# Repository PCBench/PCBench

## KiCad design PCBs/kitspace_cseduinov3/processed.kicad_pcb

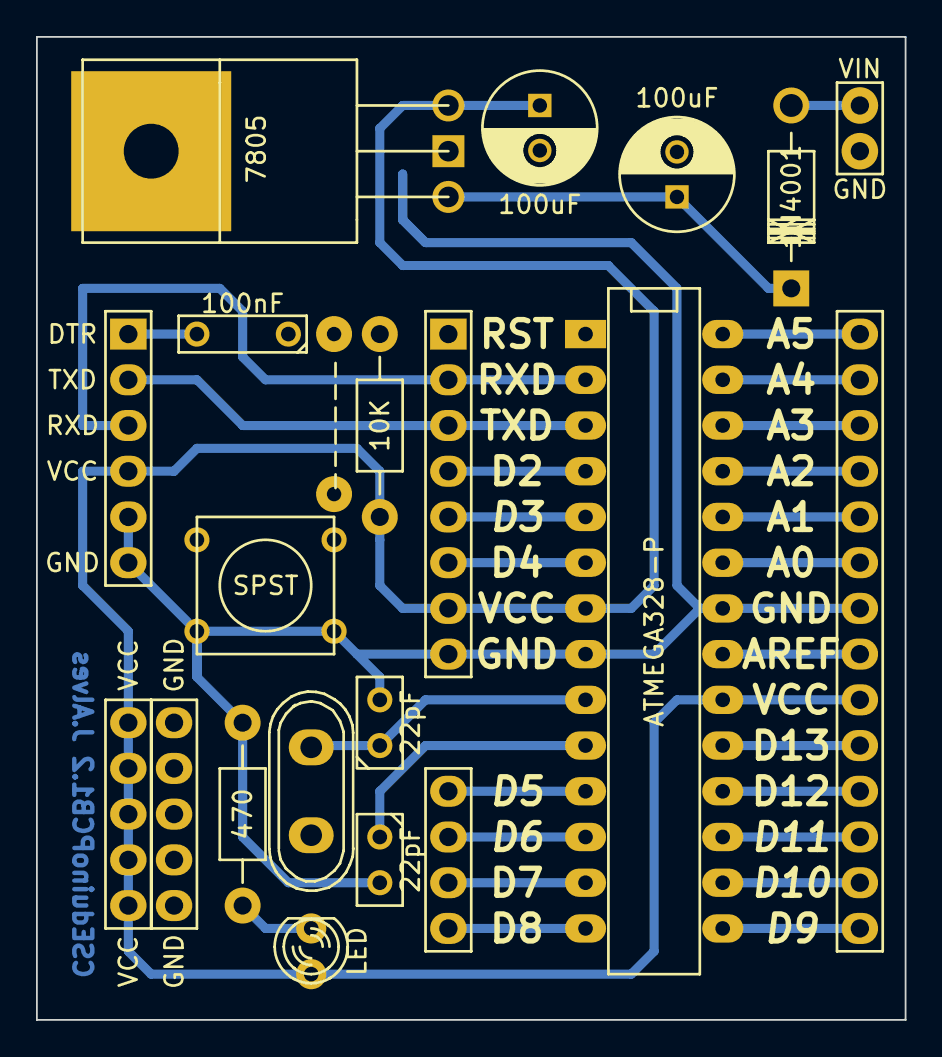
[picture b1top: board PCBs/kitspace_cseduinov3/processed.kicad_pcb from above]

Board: 2 copper layers, 48.3 x 54.6 mm, 18 parts (0 on the bottom side), 29 nets.

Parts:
C1, C2: 100uF; C_Radial_D6.3_L11.2_P2.5
C3, C4: 22pF; C1
C5: 100nF; C2
D1: 1N4001; Diode_DO-41_SOD81_Horizontal_RM10
D2: LED; LED-3MM
IC1: ATMEGA328-P; DIP-28__300_ELL
P1: CONN_01X02; Pin_Header_Straight_1x02
P2: CONN_01X14; Pin_Header_Straight_1x14
P3: CONN_01X04; Pin_Header_Straight_1x04
P4: CONN_01X08; Pin_Header_Straight_1x08
P5: CONN_01X06; Pin_Header_Straight_1x06
R1: 470; Resistor_Horizontal_RM10mm
R2: 10K; Resistor_Horizontal_RM10mm
SW1: SPST; SW_PUSH_SMALL
U1: 7805; LM78XX
X1: CRYSTAL; Crystal_HC50-U_Vertical

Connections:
+5V: C2.1, D2.1, P2.6, P4.7, R2.1
GND: C3.2, C4.2, IC1.8, P2.8, P4.8, P5.5, P5.6, R1.2, SW1.2
unnamed: C1.1, D1.2, U1.VI
unnamed: C3.1, IC1.10
unnamed: C4.1, IC1.9, X1.2
unnamed: C5.2, P5.1
unnamed: D1.1, P1.1
unnamed: D2.2, R1.1
unnamed: IC1.2, P4.2, P5.3
unnamed: IC1.3, P4.3, P5.2
unnamed: IC1.4, P4.4
unnamed: IC1.5, P4.5
unnamed: IC1.6, P4.6
unnamed: IC1.11, P3.1
unnamed: IC1.12, P3.2
unnamed: IC1.13, P3.3
unnamed: IC1.14, P3.4
unnamed: IC1.15, P2.1
unnamed: IC1.16, P2.2
unnamed: IC1.17, P2.3
unnamed: IC1.18, P2.4
unnamed: IC1.19, P2.5
unnamed: IC1.21, P2.7
unnamed: IC1.23, P2.9
unnamed: IC1.24, P2.10
unnamed: IC1.25, P2.11
unnamed: IC1.26, P2.12
unnamed: IC1.27, P2.13
unnamed: IC1.28, P2.14

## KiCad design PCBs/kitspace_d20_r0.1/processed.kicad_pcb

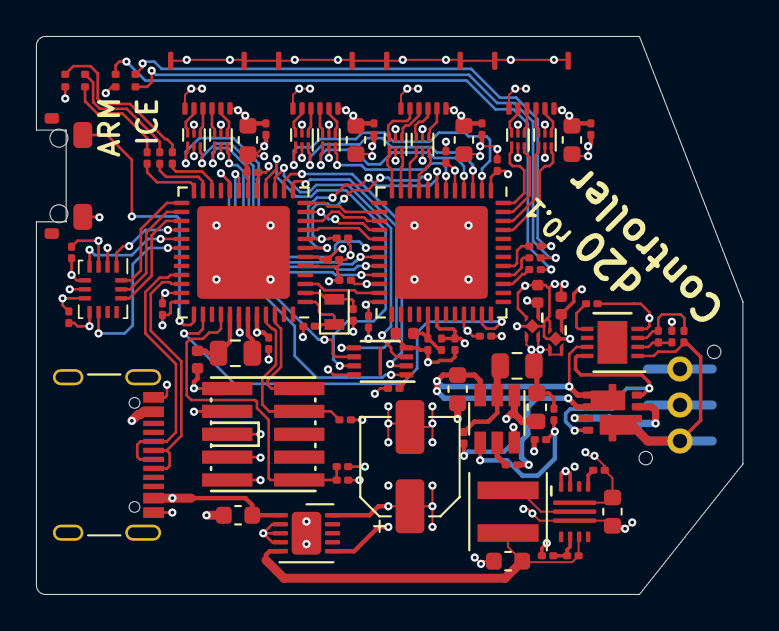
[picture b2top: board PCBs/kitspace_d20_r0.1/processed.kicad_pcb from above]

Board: 4 copper layers, 39.2 x 31.0 mm, 89 parts (1 on the bottom side), 96 nets.

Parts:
C1, C2, C4, C5, C24, C26, C28, C30, C35: 10uF; C_0603_1608Metric
C3, C10, C11, C12, C13, C17, C18, C19, C20, C21, C22, C23, C25, C27, C29, C31, C32, C33, C34: 100nF; C_0201_0603Metric
C6, C7, C8, C14: 1uF; C_0402_1005Metric
C9: CP1; CP_Elec_5x3.9
C15, C16: 22pF; C_0201_0603Metric
D1, D2: LED_ARGB; led_rbag_1515
FB1: Ferrite_Bead_Small; L_0201_0603Metric
J1: Conn_01x03; 3P_Battery_Connector
J2, J3, J4, J5: Conn_01x06_Shielded; 5034800600
J6: Conn_02x05_Odd_Even; FTSH-105-XX-X-DV
J7: USB_C_Receptacle_USB2.0; USB_C_Receptacle_Palconn_UTC16-G
L1: 1uH; L_Coilcraft_XxL4020
L2: 2.2uH; L_0805_2012Metric
L3: 10uH; L_0805_2012Metric
R1, R6: 510k; R_0201_0603Metric
R2: 25.3k; R_0201_0603Metric
R3: 34.8k; R_0201_0603Metric
R4: 750k; R_0201_0603Metric
R5, R8: 100k; R_0201_0603Metric
R7: 93.1k; R_0201_0603Metric
R9: 33.2k; R_0201_0603Metric
R10, R17, R19, R20: 10k; R_0201_0603Metric
R11, R12, R13, R14, R15, R16: 470R; R_0201_0603Metric
R18: 1k; R_0201_0603Metric
SW1: SW_Push; EVQP4
U1: LTC4367; DFN-8-1EP_3x3mm_P0.5mm_EP1.66x2.38mm
U2: AON7804; DFN3X3_8L_EP2_P
U3: TPS62135; VQFN-11_3x2mm_P0.5mm
U4: TPS561201; TSOT-23-6
U5: NP115-2.5; X2SON_4_1.0x1.0mm
U6: NP115-1.2; X2SON_4_1.0x1.0mm
U7: ATSAMD51G19A; QFN-48-1EP_7x7mm_P0.5mm_EP5.15x5.15mm
U8: ICE40UP5K-SG48ITR; QFN-48-1EP_7x7mm_P0.5mm_EP5.15x5.15mm
U9, U10, U11, U12, U13, U14, U15, U16: NC7WZ17; UDFN-6_1x1mm_P0.35mm
U17: BMX160; Bosch_LGA-14_3x2.5mm_P0.5mm
U18: AT25SF081; DFN-8-1EP_3x2mm_Pitch0.5mm
U19: LTC4413-2; DFN-10-1EP_3x3mm_P0.5mm_EP1.65x2.38mm
Y1: 32.768kHz; Crystal_SMD_2012-2Pin_2.0x1.2mm

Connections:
1v2: C7.1, C22.1, C23.1, FB1.1, U6.1, U8.5, U8.30
1v2_pll: C8.1, C21.1, FB1.2, U8.29
2v5: C6.1, C20.1, U5.1, U8.24
3v3: C5.1, C10.1, C11.1, C12.1, C13.1, C17.1, C18.1, C19.1, C33.1, C34.1, D1.1, D2.1, L2.2, R9.2, R18.2, R19.2, R20.2, U5.3, U5.4, U6.3, U6.4, U7.6, U7.17, U7.36, U7.44, U8.1, U8.22, U8.33, U17.5, U17.8, U18.8
3v3_fb: R9.1, R10.1, U4.4
4v5: C9.1, C24.1, C25.1, C26.1, C27.1, C28.1, C29.1, C30.1, C31.1, J2.1, J3.1, J4.1, J5.1, U9.5, U10.5, U11.5, U12.5, U13.5, U14.5, U15.5, U16.5, U19.6, U19.10
4v5_in: C2.1, L1.2, R6.2, U3.6, U19.5
5v0_usb: C35.1, J7.A4, J7.A9, J7.B4, J7.B9, U19.1
5v_fb: R6.1, R7.1, U3.5
unnamed: U2.2, U2.5
unnamed: U1.8, U2.3, U2.6
unnamed: R1.1, U1.5
unnamed: R3.1, R4.2, U1.3
unnamed: R2.1, R3.2, U1.2
unnamed: R5.1, U3.8
unnamed: L1.1, U3.2
unnamed: R8.1, U4.5
unnamed: C3.1, U4.6
unnamed: C3.2, L2.1, U4.2
unnamed: C14.1, L3.2, U7.41
unnamed: R11.1, U7.22
unnamed: R12.1, U7.24
unnamed: R13.1, U7.23
unnamed: C15.1, U7.1, Y1.1
unnamed: C16.1, U7.2, Y1.2
unnamed: R14.1, U8.39
unnamed: R15.1, U8.40
unnamed: R16.1, U8.41
unnamed: U7.38, U8.35
unnamed: U7.3, U8.23
unnamed: SW1.1, U7.37
unnamed: L3.1, U7.43
_led0_blank: U8.20, U9.1
_led0_data: U8.21, U9.3
_led0_latch: U8.19, U10.3
_led0_sclk: U8.18, U10.1
_led1_blank: U8.4, U11.1
_led1_data: U8.6, U11.3
_led1_latch: U8.3, U12.3
_led1_sclk: U8.2, U12.1
_led2_blank: U8.10, U13.1
_led2_data: U8.9, U13.3
_led2_latch: U8.11, U14.3
_led2_sclk: U8.12, U14.1
_led3_blank: U8.46, U15.1
_led3_data: U8.45, U15.3
_led3_latch: U8.47, U16.3
_led3_sclk: U8.48, U16.1
gnd: C1.2, C2.2, C4.2, C5.2, C6.2, C7.2, C8.2, C9.2, C10.2, C11.2, C12.2, C13.2, C14.2, C15.2, C16.2, C17.2, C18.2, C19.2, C20.2, C21.2, C22.2, C23.2, C24.2, C25.2, C26.2, C27.2, C28.2, C29.2, C30.2, C31.2, C32.2, C33.2, C34.2, C35.2, J1.3, J2.6, J2.SH, J3.6, J3.SH, J4.6, J4.SH, J5.6, J5.SH, J6.1, J6.3, J6.5, J6.7, J6.9, J7.A1, J7.A12, J7.B1, J7.B12, J7.S1, R1.2, R2.2, R7.2, R10.2, R17.2, SW1.2, U1.4, U3.3, U3.10, U3.11, U4.1, U5.2, U6.2, U7.5, U7.18, U7.35, U7.42, U7.49, U8.49, U9.2, U10.2, U11.2, U12.2, U13.2, U14.2, U15.2, U16.2, U17.2, U17.3, U17.6, U17.7, U18.4, U19.2, U19.3, U19.4, U19.11
ice_config_done: U7.7, U8.7
ice_config_miso: U7.12, U8.14
ice_config_mosi: U7.9, U8.17
ice_config_reset: R17.1, U7.8, U8.8
ice_config_sck: U7.10, U8.15
ice_config_ss: U7.11, U8.16
ice_led_b: D2.4, R16.2
ice_led_g: D2.3, R15.2
ice_led_r: D2.2, R14.2
imu_cs: U7.27, U17.12
imu_int1: U7.29, U17.4
imu_int2: U7.30, U17.9
imu_miso: U7.28, U17.1
imu_mosi: U7.25, U17.14
imu_sck: U7.26, U17.13
led0_blank: J2.3, U9.6
led0_data: J2.2, U9.4
led0_latch: J2.4, U10.4
led0_sclk: J2.5, U10.6
led1_blank: J3.3, U11.6
led1_data: J3.2, U11.4
led1_latch: J3.4, U12.4
led1_sclk: J3.5, U12.6
led2_blank: J4.3, U13.6
led2_data: J4.2, U13.4
led2_latch: J4.4, U14.4
led2_sclk: J4.5, U14.6
led3_blank: J5.3, U15.6
led3_data: J5.2, U15.4
led3_latch: J5.4, U16.4
led3_sclk: J5.5, U16.6
led_b: D1.4, R13.2
led_g: D1.3, R12.2
led_r: D1.2, R11.2
pp_batt: J1.1, R4.1, U1.1, U2.4
pp_batt_prot: C1.1, C4.1, R5.2, R8.2, U1.7, U2.1, U3.1, U4.3
qspi_bus_cs: R20.1, U7.20, U18.1
qspi_bus_io0: U7.13, U18.5
qspi_bus_io1: U7.14, U18.2
qspi_bus_io2: U7.15, U18.3
qspi_bus_io3: U7.16, U18.7
qspi_bus_sck: U7.19, U18.6
samd_rst: C32.1, J6.10, R19.1, U7.40
samd_usb_n: J7.A7, J7.B7, U7.33
samd_usb_p: J7.A6, J7.B6, U7.34
swdclk: J6.4, R18.1, U7.45
swdio: J6.2, U7.46

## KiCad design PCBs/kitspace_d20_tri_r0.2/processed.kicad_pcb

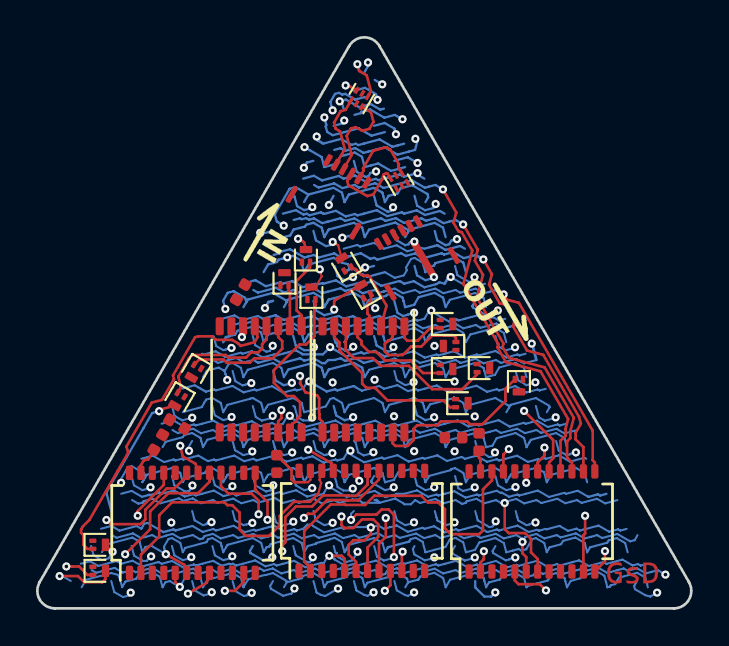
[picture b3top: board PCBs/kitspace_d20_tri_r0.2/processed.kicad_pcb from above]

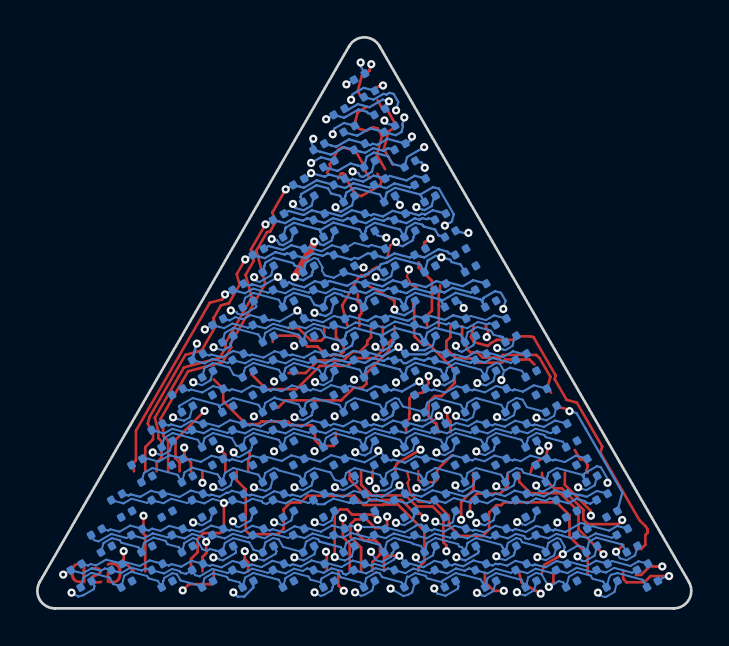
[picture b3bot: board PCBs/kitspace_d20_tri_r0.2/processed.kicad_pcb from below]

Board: 4 copper layers, 36.3 x 31.7 mm, 150 parts (120 on the bottom side), 84 nets.

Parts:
C1, C2, C3: 100nF; C_0402_1005Metric
D1, D2, D3, D4, D5, D6, D7, D8, D9, D10, D11, D12, D13, D14, D15, D17, D18, D19, D20, D21, D22, D23, D24, D25, D26, D27, D28, D29, D30, D33, D34, D35, D36, D37, D38, D39, D40, D41, D42, D43, D44, D45, D49, D50, D51, D52, D53, D54, D55, D56, D57, D58, D59, D60, D65, D66, D67, D68, D69, D70, D71, D72, D73, D74, D75, D81, D82, D83, D84, D85, D86, D87, D88, D89, D90, D97, D98, D99, D100, D101, D102, D103, D104, D105, D113, D114, D115, D116, D117, D118, D119, D120, D129, D130, D131, D132, D133, D134, D135, D145, D146, D147, D148, D149, D150, D161, D162, D163, D164, D165, D177, D178, D179, D180, D193, D194, D195, D209, D210, D225: LED_ARGB; led_rbag_1515
J1: input; 5034800600
J2: output; 5034800600
Q1, Q2, Q3, Q4, Q5, Q6, Q7, Q8, Q9, Q10, Q11, Q12, Q13, Q14, Q15: LP0404N3T5G; SOT-883
R1: 2.2k; R_0402_1005Metric
R2: 7.5k; R_0402_1005Metric
R3: 4.12k; R_0402_1005Metric
U1, U2, U3: TLC59025; SSOP-24_slim
U4, U5: 74HC595; TSSOP-16_slim
U6, U7: NC7WZ17; UDFN-6_1x1mm_P0.35mm

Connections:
U1_r_ext: R1.1, U1.23
U2_r_ext: R2.1, U2.23
U3_r_ext: R3.1, U3.23
blank: U1.21, U2.21, U3.21, U6.4
blank_i: J1.3, U6.3
colb_0: D1.2, D17.2, D33.2, D49.2, D65.2, D81.2, D97.2, D113.2, D129.2, D145.2, D161.2, D177.2, D193.2, D209.2, D225.2, U3.5
colb_1: D2.2, D18.2, D34.2, D50.2, D66.2, D82.2, D98.2, D114.2, D130.2, D146.2, D162.2, D178.2, D194.2, D210.2, U3.6
colb_3: D4.2, D20.2, D36.2, D52.2, D68.2, D84.2, D100.2, D116.2, D132.2, D148.2, D164.2, D180.2, U3.8
colb_4: D5.2, D21.2, D37.2, D53.2, D69.2, D85.2, D101.2, D117.2, D133.2, D149.2, D165.2
colb_5: D6.2, D22.2, D38.2, D54.2, D70.2, D86.2, D102.2, D118.2, D134.2, D150.2
colb_6: D7.2, D23.2, D39.2, D55.2, D71.2, D87.2, D103.2, D119.2, D135.2, U3.11
colb_7: D8.2, D24.2, D40.2, D56.2, D72.2, D88.2, D104.2, D120.2
colb_8: D9.2, D25.2, D41.2, D57.2, D73.2, D89.2, D105.2, U3.13
colb_9: D10.2, D26.2, D42.2, D58.2, D74.2, D90.2
colb_10: D11.2, D27.2, D43.2, D59.2, D75.2
colb_11: D12.2, D28.2, D44.2, D60.2, U3.16
colb_12: D13.2, D29.2, D45.2, U3.17
colb_13: D14.2, D30.2, U3.18
colb_14: D15.2, U3.19
colg_0: D1.3, D17.3, D33.3, D49.3, D65.3, D81.3, D97.3, D113.3, D129.3, D145.3, D161.3, D177.3, D193.3, D209.3, D225.3, U2.5
colg_1: D2.3, D18.3, D34.3, D50.3, D66.3, D82.3, D98.3, D114.3, D130.3, D146.3, D162.3, D178.3, D194.3, D210.3, U2.6
colg_2: D3.3, D19.3, D35.3, D51.3, D67.3, D83.3, D99.3, D115.3, D131.3, D147.3, D163.3, D179.3, D195.3, U2.7
colg_3: D4.3, D20.3, D36.3, D52.3, D68.3, D84.3, D100.3, D116.3, D132.3, D148.3, D164.3, D180.3, U2.8
colg_4: D5.3, D21.3, D37.3, D53.3, D69.3, D85.3, D101.3, D117.3, D133.3, D149.3, D165.3, U2.9
colg_5: D6.3, D22.3, D38.3, D54.3, D70.3, D86.3, D102.3, D118.3, D134.3, D150.3, U2.10
colg_6: D7.3, D23.3, D39.3, D55.3, D71.3, D103.3, D119.3, D135.3
colg_7: D8.3, D24.3, D40.3, D56.3, D72.3, D88.3, D104.3, D120.3
colg_8: D9.3, D25.3, D41.3, D57.3, D73.3, D89.3, D105.3
colg_9: D10.3, D26.3, D42.3, D58.3
colg_10: D11.3, D27.3, D43.3, D59.3, D75.3
colg_11: D12.3, D28.3, D44.3, D60.3
colg_12: D13.3, D29.3, D45.3, U2.17
colg_13: D14.3, D30.3, U2.18
colg_14: D15.3, U2.19
colr_0: D1.4, D17.4, D33.4, D49.4, D65.4, D81.4, D97.4, D113.4, D129.4, D145.4, D161.4, D177.4, D193.4, D209.4, D225.4, U1.5
colr_1: D2.4, D18.4, D34.4, D50.4, D66.4, D82.4, D98.4, D114.4, D130.4, D146.4, D162.4, D178.4, D194.4, D210.4, U1.6
colr_2: D3.4, D19.4, D35.4, D51.4, D67.4, D83.4, D99.4, D115.4, D131.4, D147.4, D163.4, D195.4, U1.7
colr_4: D5.4, D21.4, D37.4, D53.4, D69.4, D85.4, D101.4, D117.4, D133.4, D149.4, D165.4
colr_6: D7.4, D23.4, D39.4, D55.4, D71.4, D87.4, D119.4, D135.4, U1.11
colr_7: D8.4, D24.4, D40.4, D56.4, D72.4, D88.4, D104.4, D120.4, U1.12
colr_8: D9.4, D25.4, D41.4, D57.4, D73.4, D89.4, D105.4, U1.13
colr_9: D10.4, D26.4, D58.4, D74.4, D90.4, U1.14
colr_10: D11.4, D27.4, D43.4, D59.4, D75.4, U1.15
colr_11: D12.4, D28.4, D44.4, D60.4, U1.16
colr_12: D13.4, D29.4, D45.4, U1.17
colr_13: D14.4, D30.4, U1.18
colr_14: D15.4, U1.19
dat: U1.2, U6.6
dat_i: J1.2, U6.1
latch_i: J1.4, U7.3
row_0: D1.1, D5.1, D6.1, D7.1, D8.1, D9.1, D10.1, D11.1, D12.1, D13.1, D14.1, D15.1
row_1: D26.1, D27.1, D28.1, D29.1, D30.1
row_2: D35.1, D36.1, D37.1, D41.1, D42.1, D43.1, D44.1, D45.1
row_3: D50.1, D51.1, D52.1, D54.1, D55.1, D56.1, D58.1, D59.1, D60.1, Q4.3
row_4: D65.1, D66.1, D67.1, D68.1, D72.1, D73.1, D75.1, Q5.3
row_5: D82.1, D83.1, D84.1, D85.1, D86.1, D88.1, D89.1
row_6: D97.1, D98.1, D99.1, D100.1, D101.1, D102.1, D103.1, D104.1
row_7: D113.1, D114.1, D115.1, D116.1, D117.1, D118.1, D119.1, D120.1
row_8: D129.1, D130.1, D131.1, D132.1, D133.1, D134.1, Q9.3
row_9: D145.1, D146.1, D147.1, D148.1, D149.1, D150.1, Q10.3
row_10: D161.1, D162.1, D163.1, D164.1
row_11: D177.1, D178.1, D180.1
row_12: D194.1, D195.1, Q13.3
row_13: D209.1, D210.1, Q14.3
row_14: D225.1, Q15.3
sclk_i: J1.5, U7.1
sdo_U1>sdi_U2: U1.22, U2.2
sdo_U2>sdi_U3: U2.22, U3.2
sdo_U4>sdi_U5: U4.9, U5.14
srow_0: Q1.2, U4.15
srow_1: Q2.2, U4.1
srow_2: Q3.2, U4.2
srow_3: Q4.2, U4.3
srow_4: Q5.2, U4.4
srow_5: Q6.2, U4.5
srow_6: Q7.2, U4.6
srow_7: Q8.2, U4.7
srow_8: Q9.2, U5.15
srow_9: Q10.2, U5.1
srow_10: Q11.2, U5.2
srow_11: Q12.2, U5.3
srow_12: Q13.2, U5.4
srow_13: Q14.2, U5.5
srow_14: Q15.2, U5.6
